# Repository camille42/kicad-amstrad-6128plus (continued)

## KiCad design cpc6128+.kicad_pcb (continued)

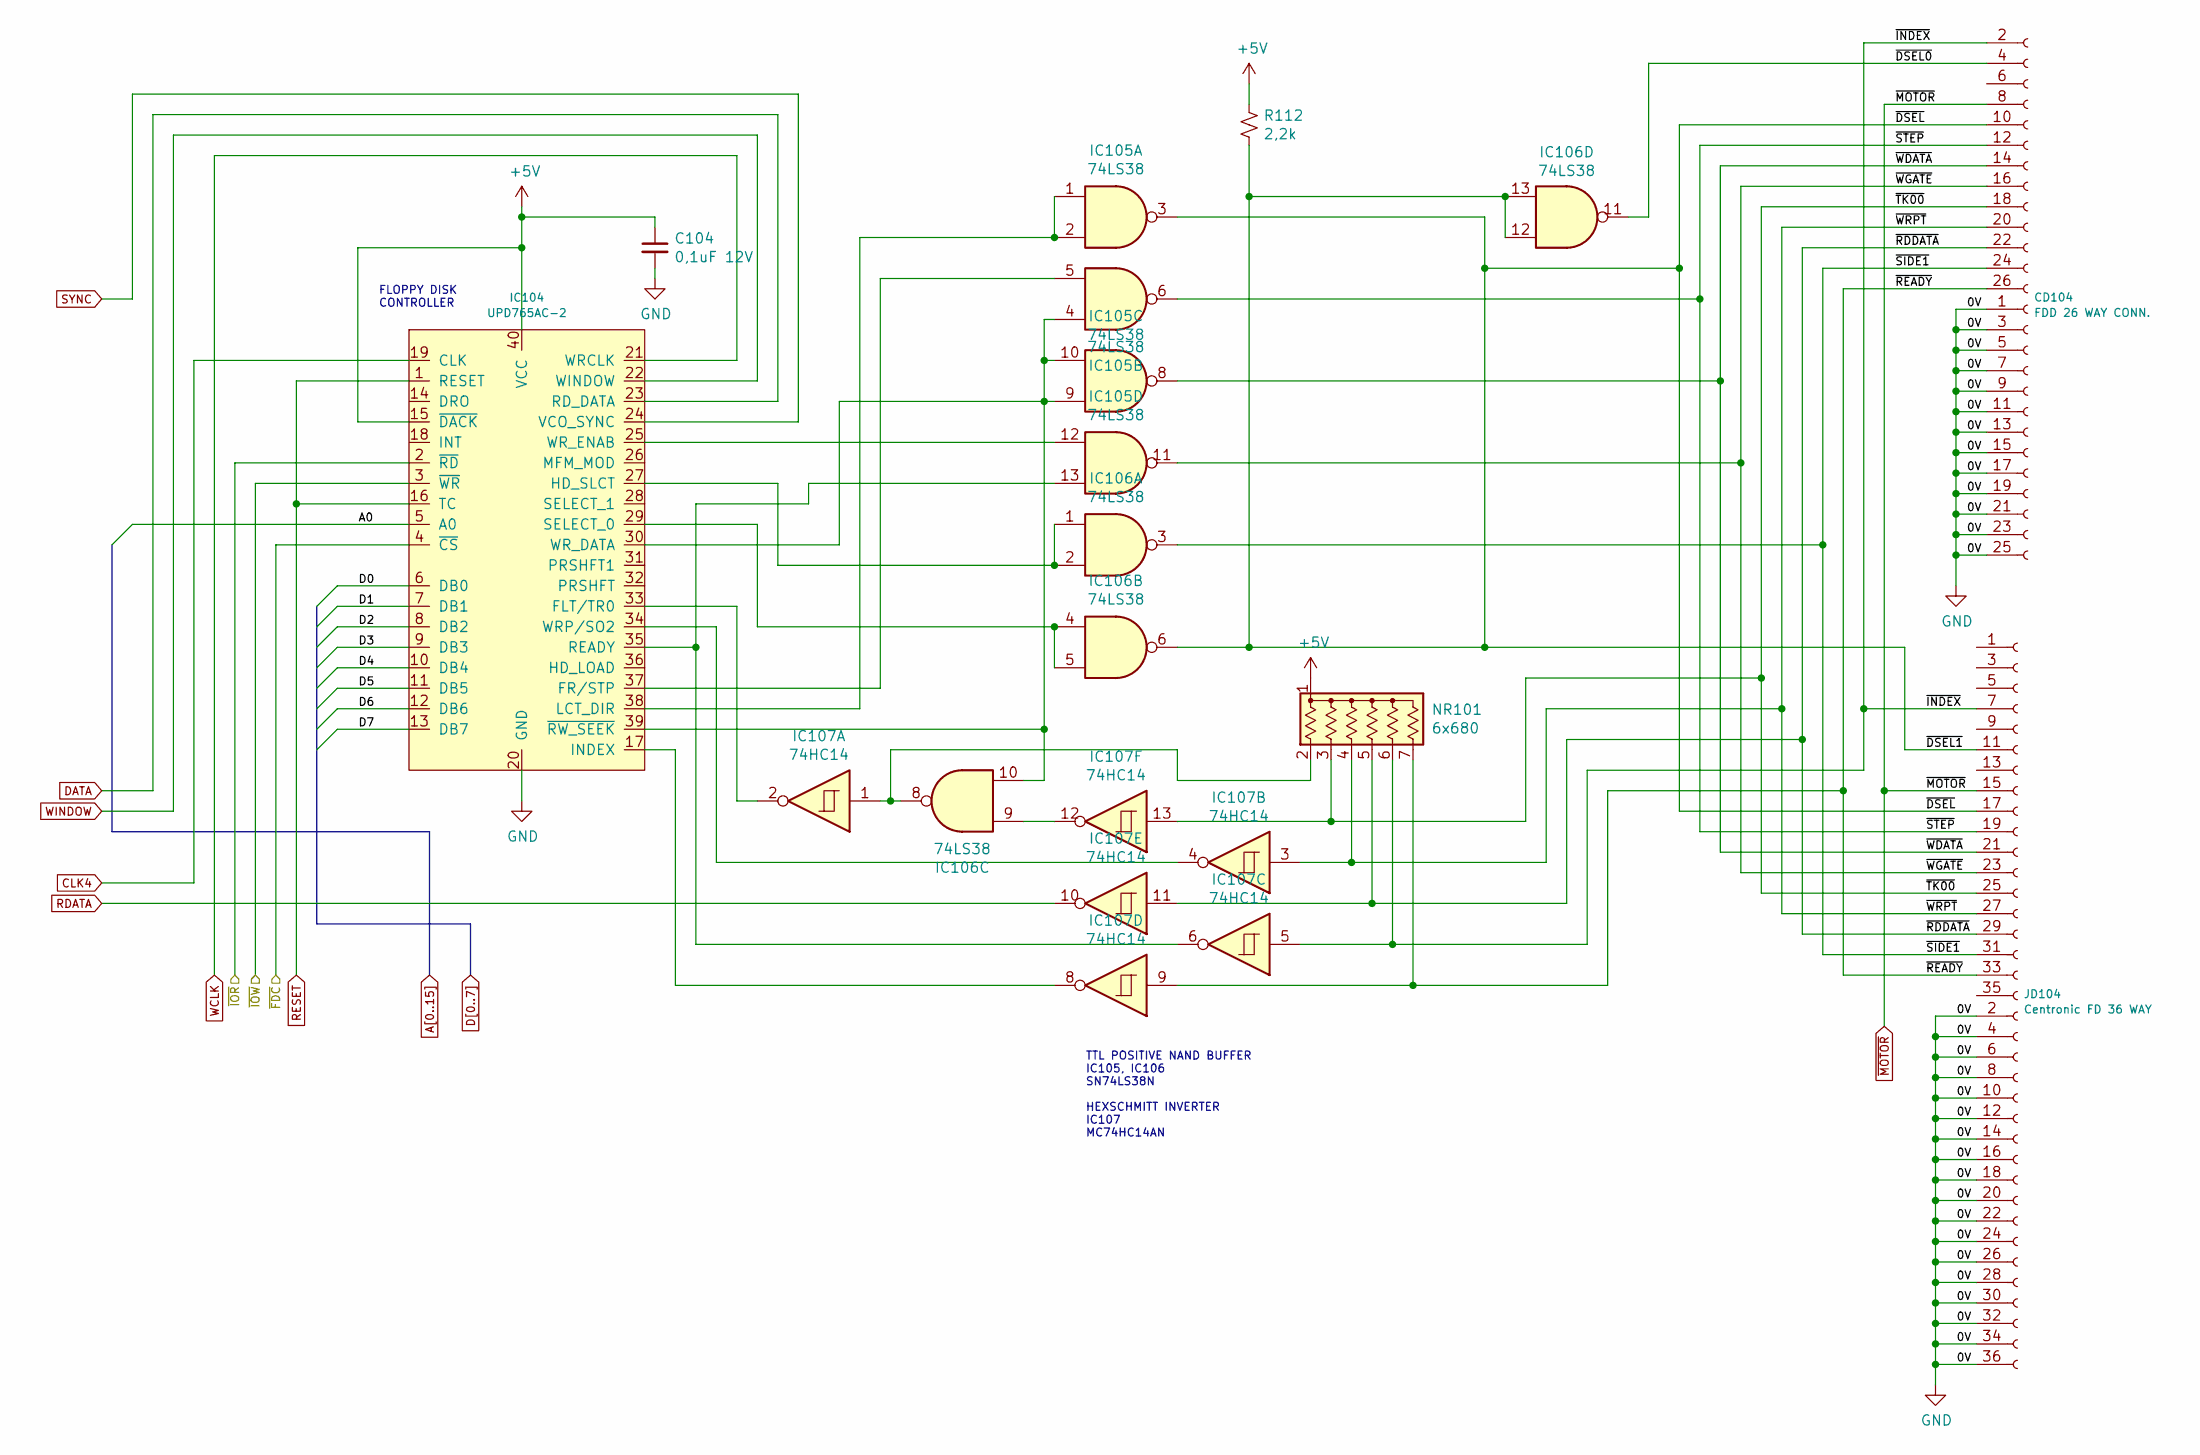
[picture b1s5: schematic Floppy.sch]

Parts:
C104: 0,1uF 12V; C_Disc_D5.0mm_W2.5mm_P5.00mm
CD104: FDD 26 WAY CONN.; Connector_Disk_2x13
IC104: UPD765AC-2; DIP-40_W15.24mm
IC105, IC106: 74LS38; DIP-14_W7.62mm
IC107: 74HC14; DIP-14_W7.62mm
JD104: Centronic FD 36 WAY; centronic_36
NR101: 6x680; R_Array_SIP7
R112: 2,2k; R_Axial_DIN0204_L3.6mm_D1.6mm_P5.08mm_Horizontal

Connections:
/FloppyDisk/~DSEL: CD104.10, IC105.3, IC106.6, IC106.12, IC106.13, JD104.11, JD104.17, R112.2
/FloppyDisk/~DSEL0: CD104.4, IC106.11
/FloppyDisk/~FDC: IC104.4 (~CS); also elsewhere on the board
/FloppyDisk/~INDEX: CD104.2, IC107.5, JD104.7, NR101.6 (R5)
/FloppyDisk/~IOR: IC104.2 (~RD); also elsewhere on the board
/FloppyDisk/~IOW: IC104.3 (~WR); also elsewhere on the board
/FloppyDisk/~RDDATA: CD104.22, IC107.11, JD104.29, NR101.5 (R4)
/FloppyDisk/~READY: CD104.26, IC107.9, JD104.33, NR101.7 (R6)
/FloppyDisk/~SIDE1: CD104.24, IC106.3, JD104.31
/FloppyDisk/~STEP: CD104.12, IC105.6, JD104.19
/FloppyDisk/~TK00: CD104.18, IC107.13, JD104.25, NR101.3 (R2)
/FloppyDisk/~WDATA: CD104.14, IC105.8, JD104.21
/FloppyDisk/~WGATE: CD104.16, IC105.11, JD104.23
/FloppyDisk/~WRPT: CD104.20, IC107.3, JD104.27, NR101.4 (R3)
A0: IC104.5 (A0); also elsewhere on the board
A8: C104.1, IC104.15 (~DACK), IC104.40 (VCC), NR101.1 (common), R112.1; also elsewhere on the board
CLK4: IC104.19 (CLK); also elsewhere on the board
D0: IC104.6 (DB0); also elsewhere on the board
D1: IC104.7 (DB1); also elsewhere on the board
D2: IC104.8 (DB2); also elsewhere on the board
D3: IC104.9 (DB3); also elsewhere on the board
D4: IC104.10 (DB4); also elsewhere on the board
D5: IC104.11 (DB5); also elsewhere on the board
D6: IC104.12 (DB6); also elsewhere on the board
D7: IC104.13 (DB7); also elsewhere on the board
DATA: IC104.23 (RD_DATA); also elsewhere on the board
unnamed: IC104.17 (INDEX), IC107.8
unnamed: IC104.25 (WR_ENAB), IC105.12
unnamed: IC104.27 (HD_SLCT), IC106.1, IC106.2
unnamed: IC104.29 (SELECT_0), IC106.4, IC106.5
unnamed: IC104.30 (WR_DATA), IC104.39 (~RW_SEEK), IC105.4, IC105.9, IC105.10, IC106.10
unnamed: IC104.33 (FLT/TR0), IC107.2
unnamed: IC104.34 (WRP/SO2), IC107.4
unnamed: IC104.35 (READY), IC105.13, IC107.6
unnamed: IC104.37 (FR/STP), IC105.5
unnamed: IC104.38 (LCT_DIR), IC105.1, IC105.2
unnamed: IC106.8, IC107.1, NR101.2 (R1)
unnamed: IC106.9, IC107.12
RDATA: IC107.10; also elsewhere on the board
RESET: IC104.1 (RESET), IC104.16 (TC); also elsewhere on the board
SYNC: IC104.24 (VCO_SYNC); also elsewhere on the board
WCLK: IC104.21 (WRCLK); also elsewhere on the board
WINDOW: IC104.22 (WINDOW); also elsewhere on the board
~MOTOR: CD104.8, JD104.15; also elsewhere on the board

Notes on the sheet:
FLOPPY DISK CONTROLLER
TTL POSITIVE NAND BUFFER IC105, IC106 SN74LS38N
HEXSCHMITT INVERTER IC107 MC74HC14AN

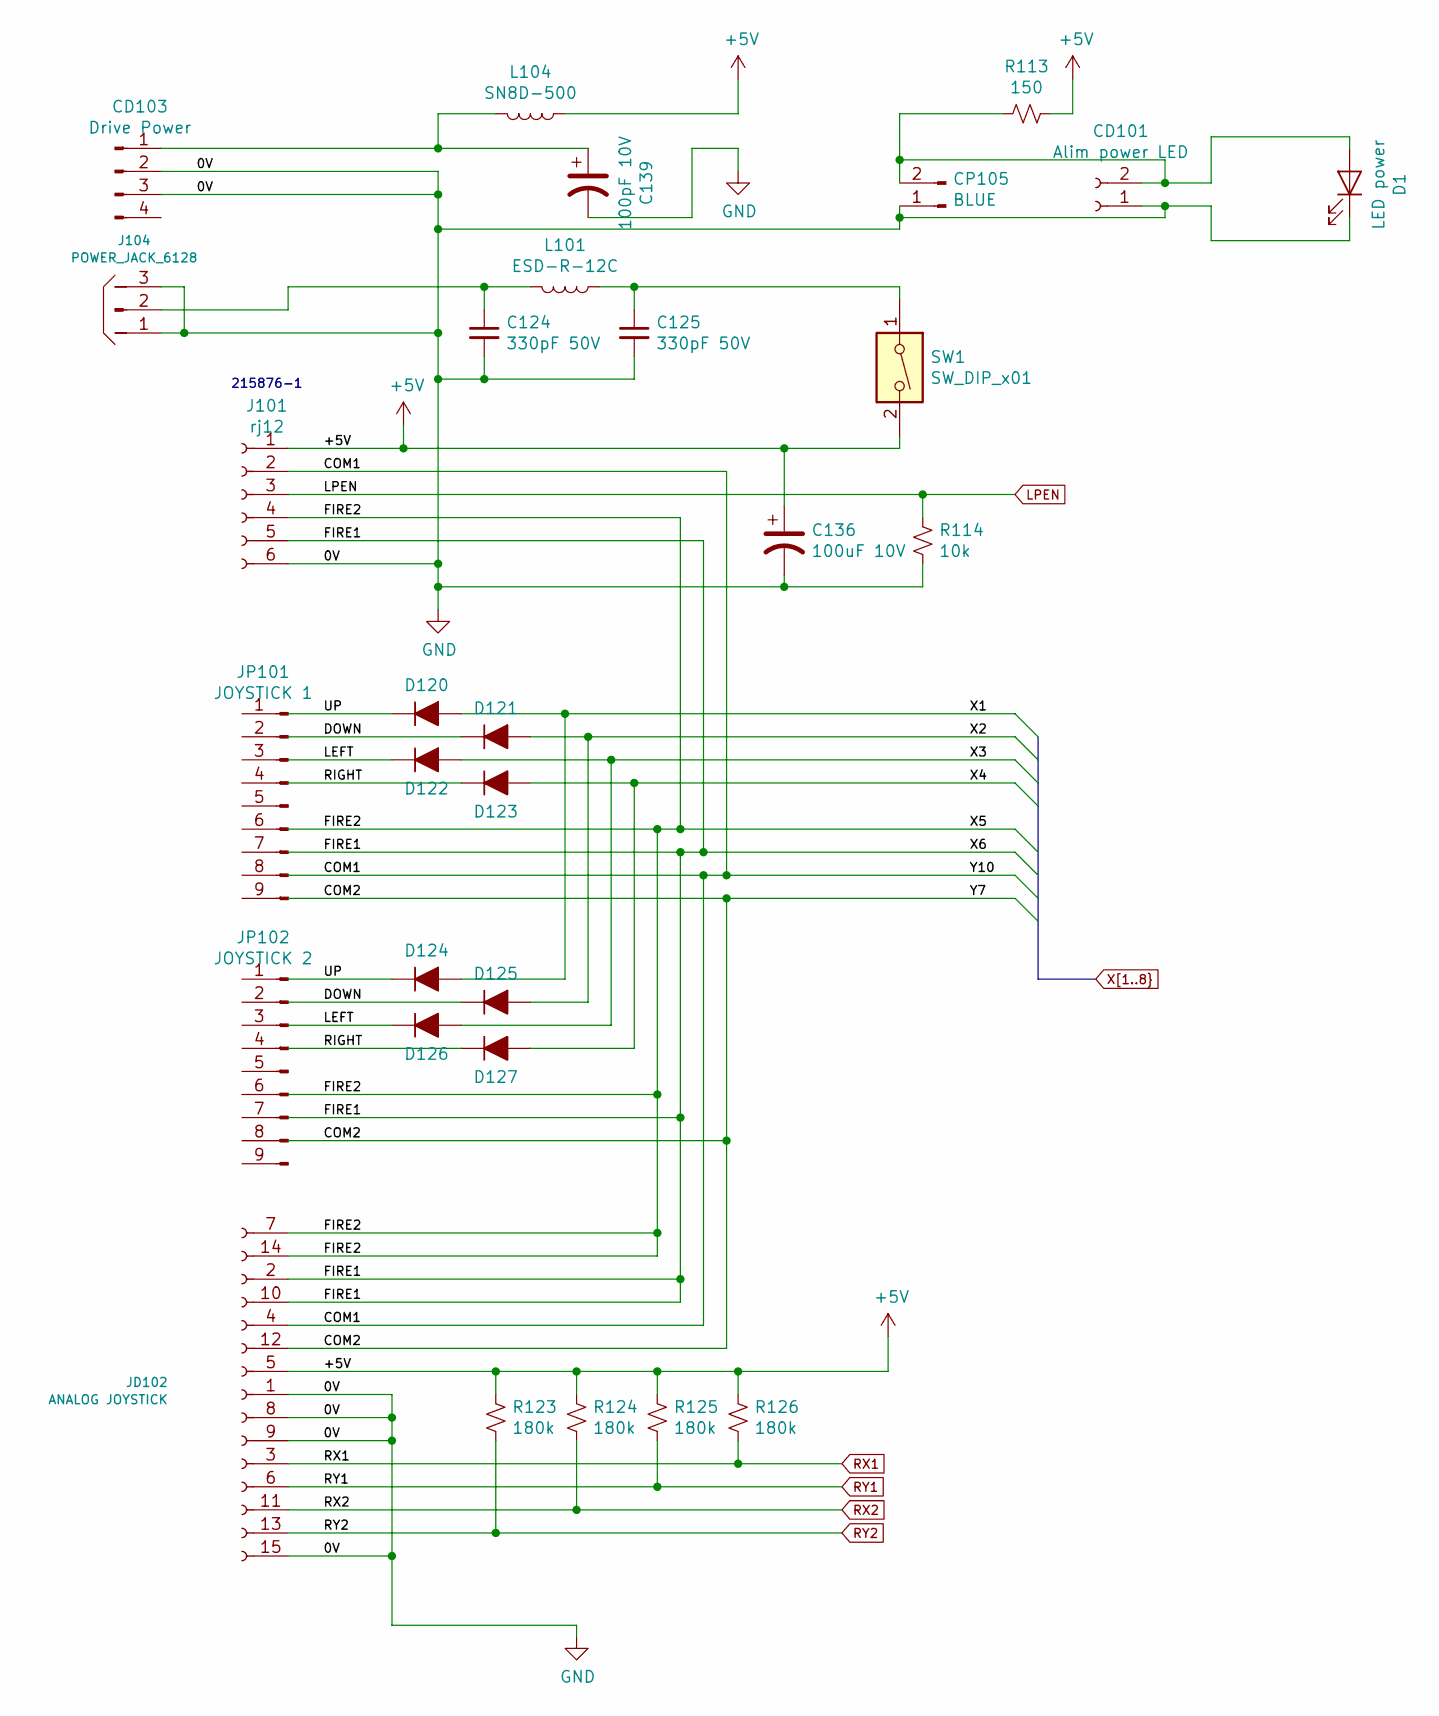
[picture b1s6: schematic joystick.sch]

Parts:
C124, C125: 330pF 50V; C_Disc_D5.0mm_W2.5mm_P5.00mm
C136: 100uF 10V; CP_Radial_D5.0mm_P2.50mm
C139: 100pF 10V; CP_Radial_D8.0mm_P5.00mm
CD101: Alim power LED; PinHeader_1x02_P1.00mm_Vertical
CD103: Drive Power; PinHeader_1x04_P1.00mm_Vertical
CP105: BLUE; PinHeader_1x02_P1.00mm_Vertical
D1: LED power; D_A-405_P5.08mm_Vertical_AnodeUp
D120: D120; D_A-405_P5.08mm_Vertical_AnodeUp
D121: D121; D_A-405_P5.08mm_Vertical_AnodeUp
D122: D122; D_A-405_P5.08mm_Vertical_AnodeUp
D123: D123; D_A-405_P5.08mm_Vertical_AnodeUp
D124: D124; D_A-405_P5.08mm_Vertical_AnodeUp
D125: D125; D_A-405_P5.08mm_Vertical_AnodeUp
D126: D126; D_A-405_P5.08mm_Vertical_AnodeUp
D127: D127; D_A-405_P5.08mm_Vertical_AnodeUp
J101: rj12; RJ12_Amphenol_54601
J104: POWER_JACK_6128; power_jack_6128
JD102: ANALOG JOYSTICK; DSUB-15_Female_Horizontal_P2.77x2.84mm_EdgePinOffset4.94mm_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
JP101: JOYSTICK 1; DSUB-9_Male_Horizontal_P2.77x2.84mm_EdgePinOffset7.70mm_Hou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
JP102: JOYSTICK 2; DSUB-9_Male_Horizontal_P2.77x2.84mm_EdgePinOffset7.70mm_Hou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
L101: ESD-R-12C; L_Toroid_Vertical_L17_P17
L104: SN8D-500; L_Toroid_Vertical_L13_P13
R113: 150; R_Axial_DIN0204_L3.6mm_D1.6mm_P5.08mm_Horizontal
R114: 10k; R_Axial_DIN0204_L3.6mm_D1.6mm_P5.08mm_Horizontal
R123, R124, R125, R126: 180k; R_Axial_DIN0204_L3.6mm_D1.6mm_P5.08mm_Horizontal
SW1: SW_DIP_x01; PinHeader_1x02_P2.54mm_Vertical

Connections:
/joystick/COM1: J101.2, JD102.4
/joystick/COM2: JD102.12
/joystick/DOWN: D121.1 (K), D125.1 (K)
/joystick/FIRE1: J101.5, JD102.2, JD102.10
/joystick/FIRE2: J101.4, JD102.7, JD102.14
/joystick/LEFT: D122.1 (K), D126.1 (K)
/joystick/RIGHT: D123.1 (K), D127.1 (K)
/joystick/UP: D120.1 (K), D124.1 (K)
/joystick/X1: D120.2 (A), D124.2 (A)
/joystick/X2: D121.2 (A), D125.2 (A)
/joystick/X3: D122.2 (A), D126.2 (A)
/joystick/X4: D123.2 (A), D127.2 (A)
A8: C136.1, J101.1, JD102.5, L104.1, R113.1, R123.1, R124.1, R125.1, R126.1, SW1.2; also elsewhere on the board
LPEN: J101.3, R114.1; also elsewhere on the board
unnamed: C124.1, J104.2, L101.2
unnamed: C125.1, L101.1, SW1.1
unnamed: C139.1, CD103.1, L104.2
unnamed: CD101.2, CP105.2, D1.2 (A), R113.2
unnamed 207: JP101.2; also elsewhere on the board
unnamed 208: JP101.3; also elsewhere on the board
unnamed 209: JP101.4; also elsewhere on the board
unnamed 211: JP101.6; also elsewhere on the board
unnamed 212: JP101.7; also elsewhere on the board
unnamed 213: JP101.8; also elsewhere on the board
unnamed 214: JP101.9; also elsewhere on the board
unnamed 216: JP102.2; also elsewhere on the board
unnamed 222: JP102.8; also elsewhere on the board
RX1: JD102.3, R126.2; also elsewhere on the board
RX2: JD102.11, R124.2; also elsewhere on the board
RY1: JD102.6, R125.2; also elsewhere on the board
RY2: JD102.13, R123.2; also elsewhere on the board

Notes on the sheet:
215876-1

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
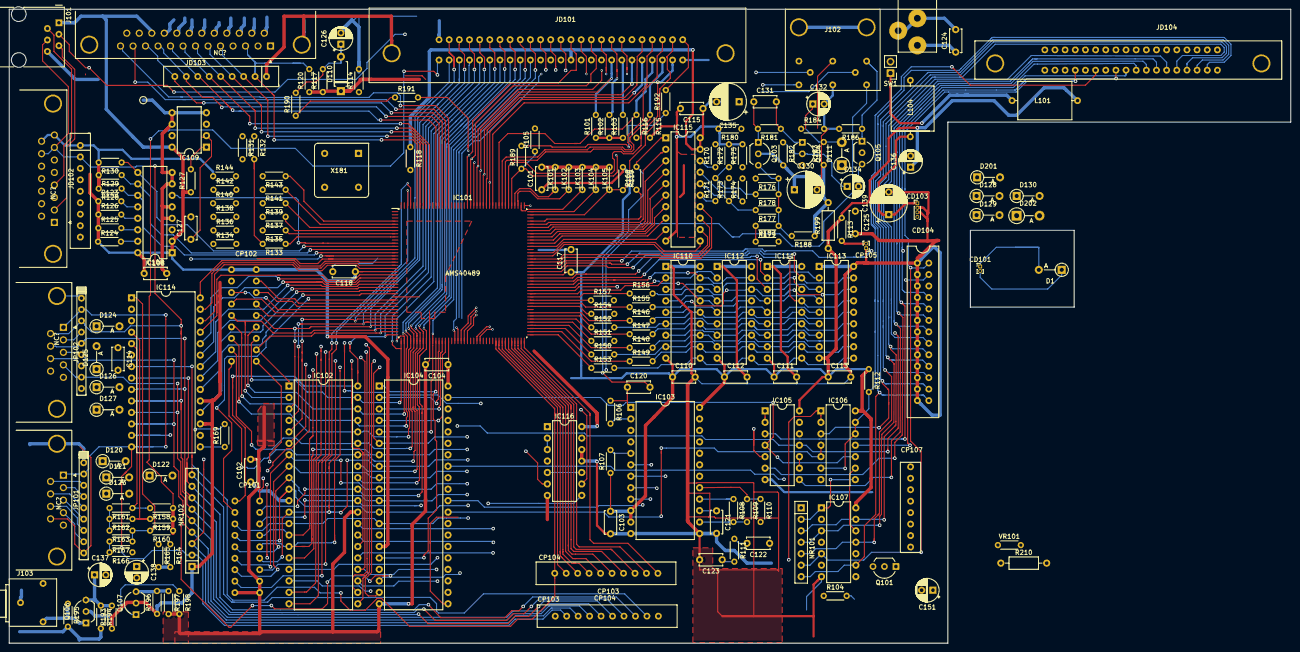
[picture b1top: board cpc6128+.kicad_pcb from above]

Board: 2 copper layers, 284.0 x 140.5 mm, 200 parts (0 on the bottom side), 264 nets.

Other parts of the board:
C110, C111, C112, C113: 0,1uF 12V; C_Disc_D5.0mm_W2.5mm_P5.00mm
IC110, IC111, IC112, IC113: 41464; DIP-18_W7.62mm
NC?: nc_db25_db15
NC?#2, NC?#3: nc_db9
NC?#4: nc_db25_db15

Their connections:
/gateArray/BUSY: NC?.8; also elsewhere on the board
/gateArray/PR1: NC?.1; also elsewhere on the board
/gateArray/PR2: NC?.2; also elsewhere on the board
/gateArray/PR3: NC?.3; also elsewhere on the board
/gateArray/PR4: NC?.4; also elsewhere on the board
/gateArray/PR5: NC?.5; also elsewhere on the board
/gateArray/PR6: NC?.6; also elsewhere on the board
/gateArray/PR7: NC?.7; also elsewhere on the board
/memoire/nwe: IC110.4, IC111.4, IC112.4, IC113.4
A8: C110.1, C111.1, C112.1, C113.1, IC110.9, IC111.9, IC112.9, IC113.9; also elsewhere on the board
unnamed 207: NC?#3.6; also elsewhere on the board
unnamed 208: NC?#3.4; also elsewhere on the board
unnamed 209: NC?#3.2; also elsewhere on the board
unnamed 211: NC?#3.7; also elsewhere on the board
unnamed 212: NC?#3.5; also elsewhere on the board
unnamed 213: NC?#3.3; also elsewhere on the board
unnamed 214: NC?#3.1; also elsewhere on the board
unnamed 216: NC?#2.6; also elsewhere on the board
unnamed 222: NC?#2.3; also elsewhere on the board
RA0: IC110.14, IC111.14, IC112.14, IC113.14; also elsewhere on the board
RA1: IC110.13, IC111.13, IC112.13, IC113.13; also elsewhere on the board
RA2: IC110.12, IC111.12, IC112.12, IC113.12; also elsewhere on the board
RA3: IC110.11, IC111.11, IC112.11, IC113.11; also elsewhere on the board
RA4: IC110.8, IC111.8, IC112.8, IC113.8; also elsewhere on the board
RA5: IC110.7, IC111.7, IC112.7, IC113.7; also elsewhere on the board
RA6: IC110.6, IC111.6, IC112.6, IC113.6; also elsewhere on the board
RA7: IC110.10, IC111.10, IC112.10, IC113.10; also elsewhere on the board
RD0: IC110.2, IC112.2; also elsewhere on the board
RD1: IC110.3, IC112.3; also elsewhere on the board
RD2: IC110.15, IC112.15; also elsewhere on the board
RD3: IC110.17, IC112.17; also elsewhere on the board
RD4: IC111.2, IC113.2; also elsewhere on the board
RD5: IC111.3, IC113.3; also elsewhere on the board
RD6: IC111.15, IC113.15; also elsewhere on the board
RD7: IC111.17, IC113.17; also elsewhere on the board
X3: NC?#2.5; also elsewhere on the board
X4: NC?#2.7, NC?#4.8; also elsewhere on the board
X5: NC?#2.2; also elsewhere on the board
X6: NC?#2.4; also elsewhere on the board
X8: NC?#2.8, NC?#3.8; also elsewhere on the board
~CAS0: IC110.16, IC111.16; also elsewhere on the board
~CAS1: IC112.16, IC113.16; also elsewhere on the board
~RAS: IC110.5, IC111.5, IC112.5, IC113.5; also elsewhere on the board

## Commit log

2021-03-25 First upload
    With a lot of errors, need a lot of work
2021-03-25 message
2021-03-25 message 2
2021-03-25 more accurate on pins definition, power, centronic 36, jack, and some wiring
2021-03-26 finished the centronic 36, some more refinements on placement, new footprint for some connectors
2021-03-26 Cabled the keyboard
2021-03-29 29-03-2021 : first usage of hierarchical labels. focus on CPU/ Cartridge Connector
2021-03-30 finished work on Z80
2021-04-08 More work on the db25 part, & the 50 way centronic connector
2021-04-09 More work on centronics port.
2021-06-01 work around IC14
2021-06-02 work on sound chip : A,B,C & X8
2021-06-04 Work on the sound Part, close to the Audio Jack. correction of Q_NPN_ECB
